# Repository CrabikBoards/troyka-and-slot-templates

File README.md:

# Templates of Troyka modules and the Crabik Slot main board

This repository stores project templates for creating your own Troyka modules or base boards based on the Crabik Slot design. You can read more about Troyka modules on the [Amperka Wiki (ru)](http://wiki.amperka.ru/troyka-modules).

## PCB Text and Markings Guidelines

### Font and Text Size
- Font: "Fredoka One" (Bold) - embedded in PCB files
- Standard text size: 1.1 mm

### Logos and DataMatrix
- Recommended logo size: 6 x 6 mm
- DataMatrix with part number: 6 x 6 mm

## [Troyka Base Module](https://github.com/CrabikBoards/troyka-and-slot-templates/tree/main/troyka-base-module)

## [Troyka I2C Module](https://github.com/CrabikBoards/troyka-and-slot-templates/tree/main/troyka-i2c-module)

## [Troyka SPI Module](https://github.com/CrabikBoards/troyka-and-slot-templates/tree/main/troyka-spi-module)

## [Troyka UART Module](https://github.com/CrabikBoards/troyka-and-slot-templates/tree/main/troyka-uart-module)

## [Troyka 2-unit Module](https://github.com/CrabikBoards/troyka-and-slot-templates/tree/main/troyka-2unit-module)

## [Crabik Slot Main board](https://github.com/CrabikBoards/troyka-and-slot-templates/tree/main/crabik-slot-template)

## Licenses

Schematics and board designs (KiCad projects), distributed as open hardware and available under [CERN-OHL-W v2](https://ohwr.org/cern_ohl_w_v2.pdf) license.

The Fredoka One font embedded in PCB files is licensed under the [SIL Open Font License, Version 1.1](https://openfontlicense.org). Copyright 2016 The Fredoka Project Authors ([https://github.com/hafontia/Fredoka-One](https://github.com/hafontia/Fredoka-One)).

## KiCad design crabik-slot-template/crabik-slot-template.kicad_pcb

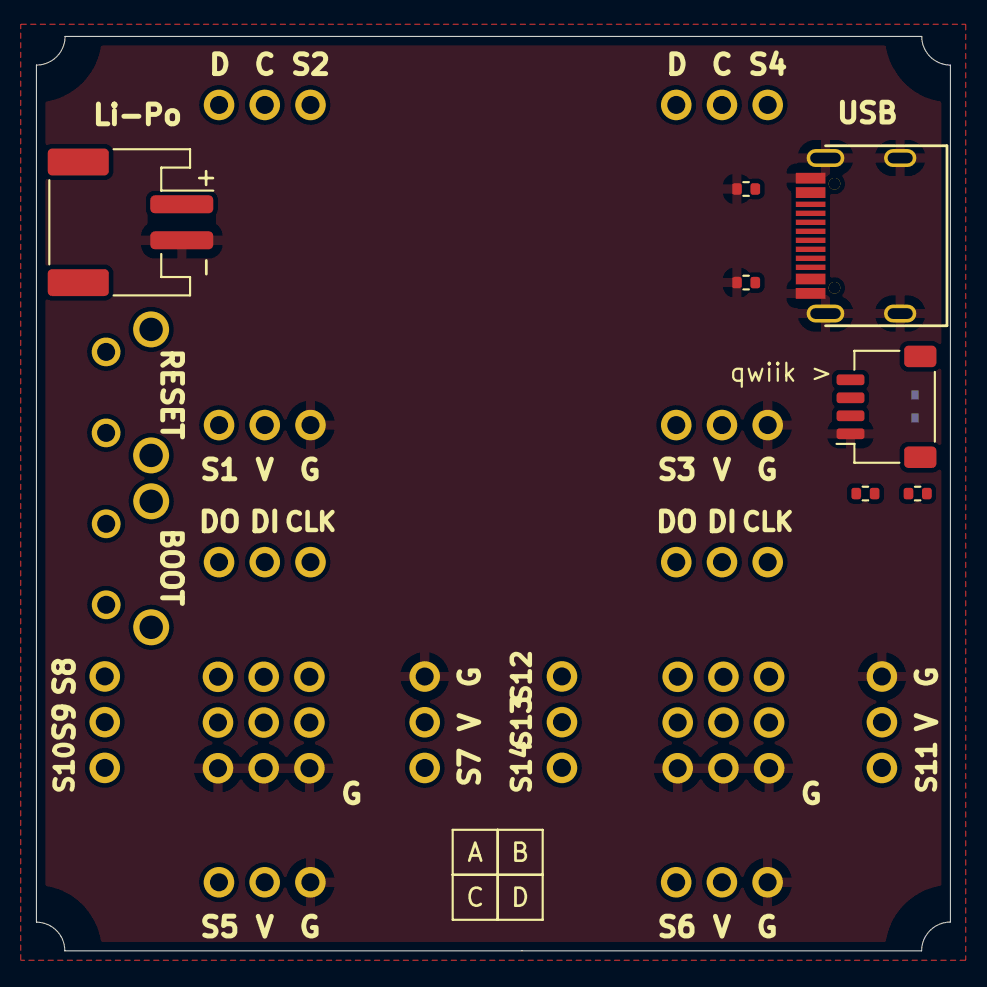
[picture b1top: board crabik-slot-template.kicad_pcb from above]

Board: 2 copper layers, 50.8 x 50.8 mm, 28 parts (1 on the bottom side), 12 nets, no tracks yet.

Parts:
J1: Battery; JST_PH_S2B-PH-SM4-TB_1x02-1MP_P2.00mm_Horizontal
J2: QWIIC; JST_SH_SM04B-SRSS-TB_1x04-1MP_P1.00mm_Horizontal
J3, J4, J6, J8, J9, J14: UP (A); PinSocket_1x03_P2.54mm_Vertical
J5, J7: DOWN (A); PinSocket_1x03_P2.54mm_Vertical
J10, J12: UP (B); PinSocket_1x03_P2.54mm_Vertical
J11, J13: DOWN (B); PinSocket_1x03_P2.54mm_Vertical
J15: CENTER (C) (1); PinHeader_1x03_P2.54mm_Vertical
J16: CENTER (D) (1); PinHeader_1x03_P2.54mm_Vertical
J17: CENTER (C) (2); PinHeader_1x03_P2.54mm_Vertical
J18: CENTER (D) (2); PinHeader_1x03_P2.54mm_Vertical
J19: CENTER (C) (3); PinHeader_1x03_P2.54mm_Vertical
J20: CENTER (D) (3); PinHeader_1x03_P2.54mm_Vertical
JP2: Set I2C Pull-Up; SolderJumper-3_P1.3mm_Bridged12_RoundedPad1.0x1.5mm_копия
P1: USB-C; TYPE-C16PIN
R2, R4: 5.1 kOhm; R_0402_1005Metric
R8, R11: 10 kOhm; R_0402_1005Metric
SW1, SW2: Reset button; KEY-TH_4P-L7.1-W5.0-P4.50-LS2.5

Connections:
3.3V: J2.2, JP2.2 (C)
C: J2.4, J4.2, J10.2, R11.2
CLK: J6.3, J12.3
D: J2.3, J4.1, J10.1, R8.2
DI: J6.2, J12.2
DO: J6.1, J12.1
GND: J1.2, J2.1, J5.3, J7.3, J8.3, J11.3, J13.3, J14.3, J15.3, J16.3, J17.3, J18.3, J19.3, J20.3, P1.A1 (GND), P1.S1 (SHIELD), R2.2, R4.2
unnamed: JP2.1 (A), R11.1
unnamed: JP2.3 (B), R8.1
unnamed: P1.A5 (CC), R4.1
unnamed: P1.B5 (VCONN), R2.1
V: J5.2, J7.2, J8.2, J11.2, J13.2, J14.2, J15.2, J16.2, J17.2, J18.2, J19.2, J20.2

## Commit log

2023-02-08 Uploading templates and editing the README, adding a license
2023-02-08 Add links
2023-02-08 Add sponsor link to project
2025-08-05 Update templates and CI
2025-08-05 Update images in CI workflow
2025-08-05 Update artifacts path
2025-08-06 Change readme and add custom font
2025-08-06 Change 3d view settings
2025-08-06 Change readme
2025-08-06 Change rendering step
2025-08-06 Remove unused files
